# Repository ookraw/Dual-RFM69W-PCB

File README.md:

Dual RFM69W Transceiver PCB
---------------------------

Designed by Felix Baessler, felix.baessler@gmail.com

The project focuses on the minimization of the costs for connectors and enclosure which quite often even exceed the prize 
you pay for your electronic components. In our daily use, a standard SD card box (ca. 53x43x7 mm) and a couple of steel needles did the job.

### Features:
The HRD_S2.zip file contains all that is required to produce a PCB that fits into a SD card box : <br/> 

- &nbsp;**2 Hope rfm69w radio modules** placed on a common bus
- &nbsp;**1 Arduino compatible mini pro 3.3V (MEGA328P)** microcontroller <br/>
- **10 standard Dupont connectors** fixed in 0.8 mm slots <br/>
  for the attachmant of 2 antennas and a USB-Serial dongle 

### LICENSE
This project is released under [CC-BY-NC 4.0](https://creativecommons.org/licenses/by-nc/4.0/).<br/>
The licensing TLDR is: You are free to use, copy, distribute and transmit this Material for personal, non-commercial purposes, as long as you give attribution and share any modifications under the same license. Commercial or for-profit use requires a license. <br/>
For more details see the [LICENSE](https://github.com/ookraw/Dual-RFM69W-PCB/blob/master/LICENSE)

### Context
The described setup serves as a reference for the [OOK Raw Data Receiver](https://github.com/ookraw/OOK-Raw-Data-Receiver)

### Special Requirement
The enclosed zip-file specifies ten 0.8 mm slots. Make sure that these slots will be edge plated : <br/>
on the top and on the buttom layer and also on the inner side of the slots, like a through hole.

### Project Presentation
An assembled prototype is presented here:  https://sites.google.com/site/rfm69arduino

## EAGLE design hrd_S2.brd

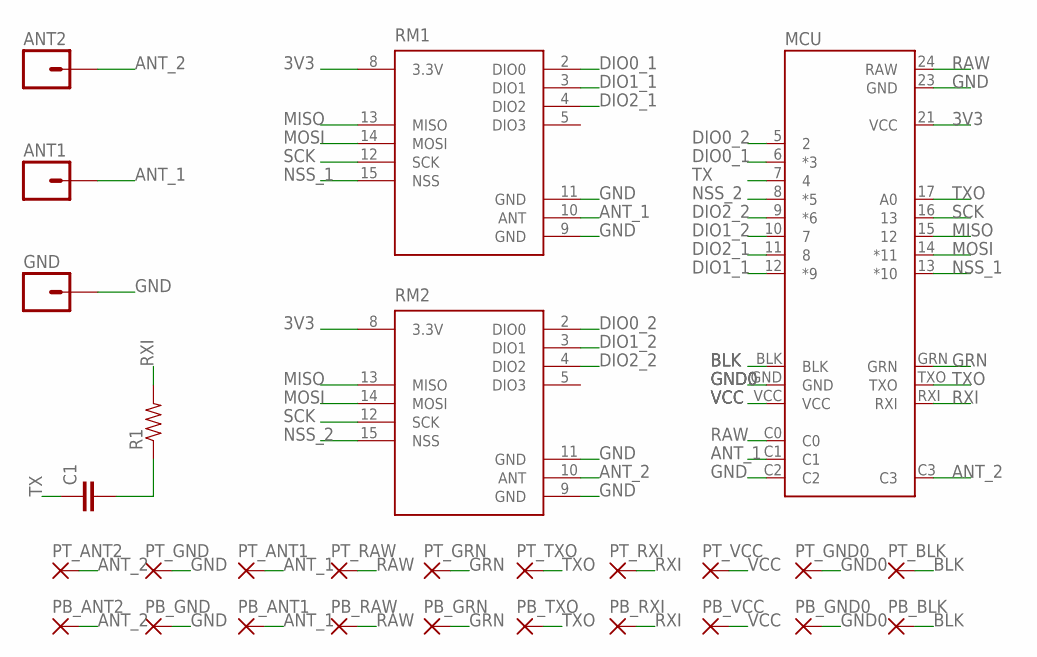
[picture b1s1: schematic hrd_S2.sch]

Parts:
ANT1, ANT2: M01PTH; 1X01
C1: CAP0805; 0805
GND: M01PTH; 1X01
MCU: APM
PB_ANT1, PB_ANT2: SMD2; SMDSLOT
PB_BLK: SMD2; SMDSLOT
PB_GND, PB_GND0: SMD2; SMDSLOT
PB_GRN: SMD2; SMDSLOT
PB_RAW: SMD2; SMDSLOT
PB_RXI: SMD2; SMDSLOT
PB_TXO: SMD2; SMDSLOT
PB_VCC: SMD2; SMDSLOT
PT_ANT1, PT_ANT2: SMD2; SMDSLOT
PT_BLK: SMD2; SMDSLOT
PT_GND, PT_GND0: SMD2; SMDSLOT
PT_GRN: SMD2; SMDSLOT
PT_RAW: SMD2; SMDSLOT
PT_RXI: SMD2; SMDSLOT
PT_TXO: SMD2; SMDSLOT
PT_VCC: SMD2; SMDSLOT
R1: RESISTOR0805-RES; 0805
RM1, RM2: RFM69HW; RFM69W-XXXS2

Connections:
3V3: MCU.21 (VCC), RM1.8 (3.3V), RM2.8 (3.3V)
ANT_1: ANT1.1, MCU.C1, PB_ANT1.1, PT_ANT1.1, RM1.10 (ANT)
ANT_2: ANT2.1, MCU.C3, PB_ANT2.1, PT_ANT2.1, RM2.10 (ANT)
BLK: MCU.BLK, PB_BLK.1, PT_BLK.1
DIO0_1: MCU.6 (*3), RM1.2 (DIO0)
DIO0_2: MCU.5 (2), RM2.2 (DIO0)
DIO1_1: MCU.12 (*9), RM1.3 (DIO1)
DIO1_2: MCU.10 (7), RM2.3 (DIO1)
DIO2_1: MCU.11 (8), RM1.4 (DIO2)
DIO2_2: MCU.9 (*6), RM2.4 (DIO2)
GND: GND.1, MCU.23 (GND), MCU.C2, PB_GND.1, PT_GND.1, RM1.9 (GND), RM1.11 (GND), RM2.9 (GND), RM2.11 (GND)
GND0: MCU.GND, PB_GND0.1, PT_GND0.1
GRN: MCU.GRN, PB_GRN.1, PT_GRN.1
MISO: MCU.15 (12), RM1.13 (MISO), RM2.13 (MISO)
MOSI: MCU.14 (*11), RM1.14 (MOSI), RM2.14 (MOSI)
unnamed: C1.2, R1.1
NSS_1: MCU.13 (*10), RM1.15 (NSS)
NSS_2: MCU.8 (*5), RM2.15 (NSS)
RAW: MCU.24 (RAW), MCU.C0, PB_RAW.1, PT_RAW.1
RXI: MCU.RXI, PB_RXI.1, PT_RXI.1, R1.2
SCK: MCU.16 (13), RM1.12 (SCK), RM2.12 (SCK)
TX: C1.1, MCU.7 (4)
TXO: MCU.17 (A0), MCU.TXO, PB_TXO.1, PT_TXO.1
VCC: MCU.VCC, PB_VCC.1, PT_VCC.1

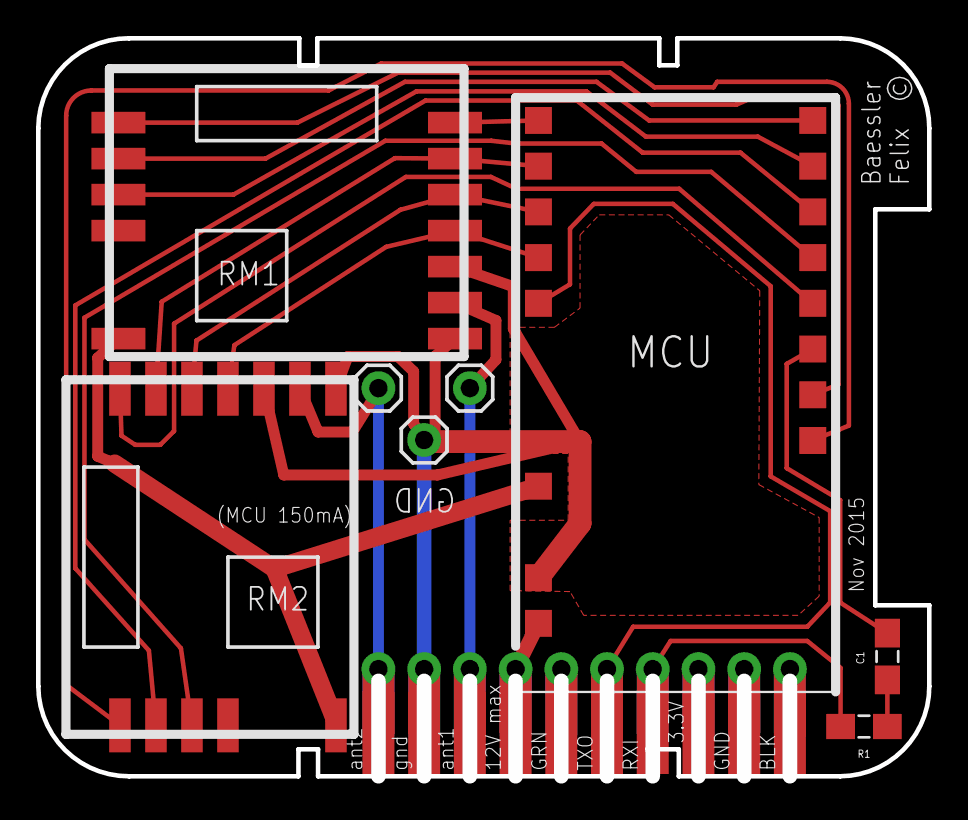
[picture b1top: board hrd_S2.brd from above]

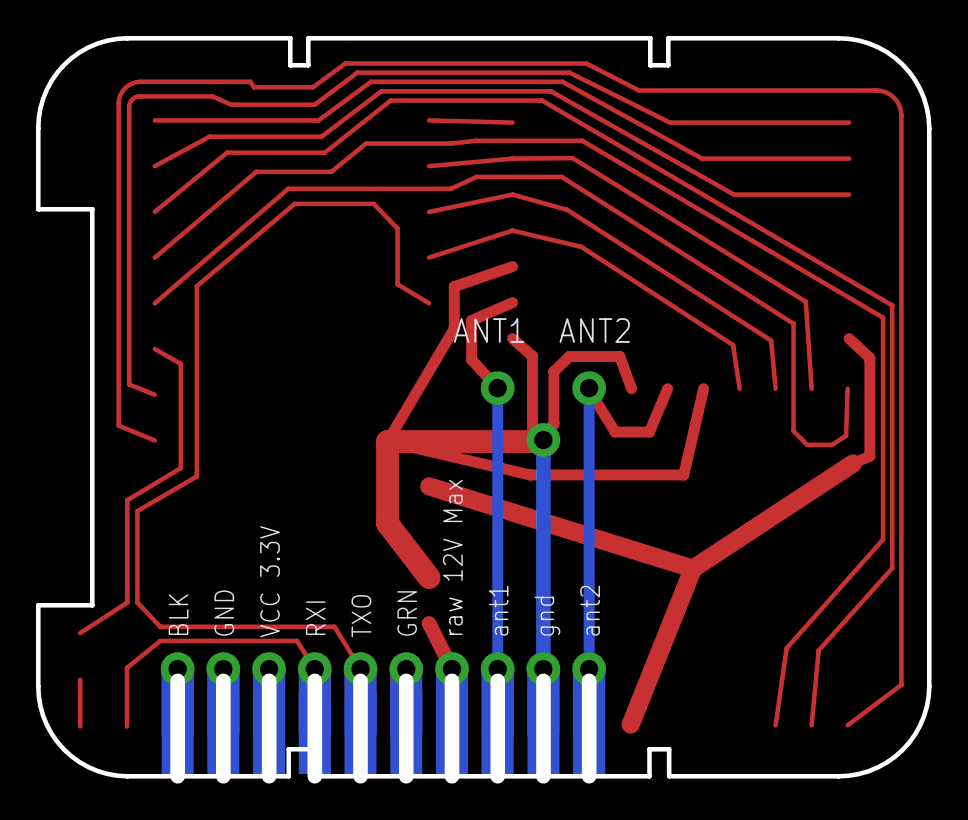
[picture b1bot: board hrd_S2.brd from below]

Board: 2 copper layers, 48.9 x 40.7 mm, 28 parts (10 on the bottom side), 24 nets.

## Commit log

2020-10-22 Create . gitignore

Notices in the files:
parts and their libraries:
SparkFun-Capacitors: Licensing: Creative Commons ShareAlike 4.0 International - https://creativecommons.org/licenses/by-sa/4.0
